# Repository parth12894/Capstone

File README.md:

# Capstone
Code and PCB files for PP01 - 5 Axis CNC Machine Controller
* The main code files for the project are located in /master/CNC/CNC/CNC_5AXIS

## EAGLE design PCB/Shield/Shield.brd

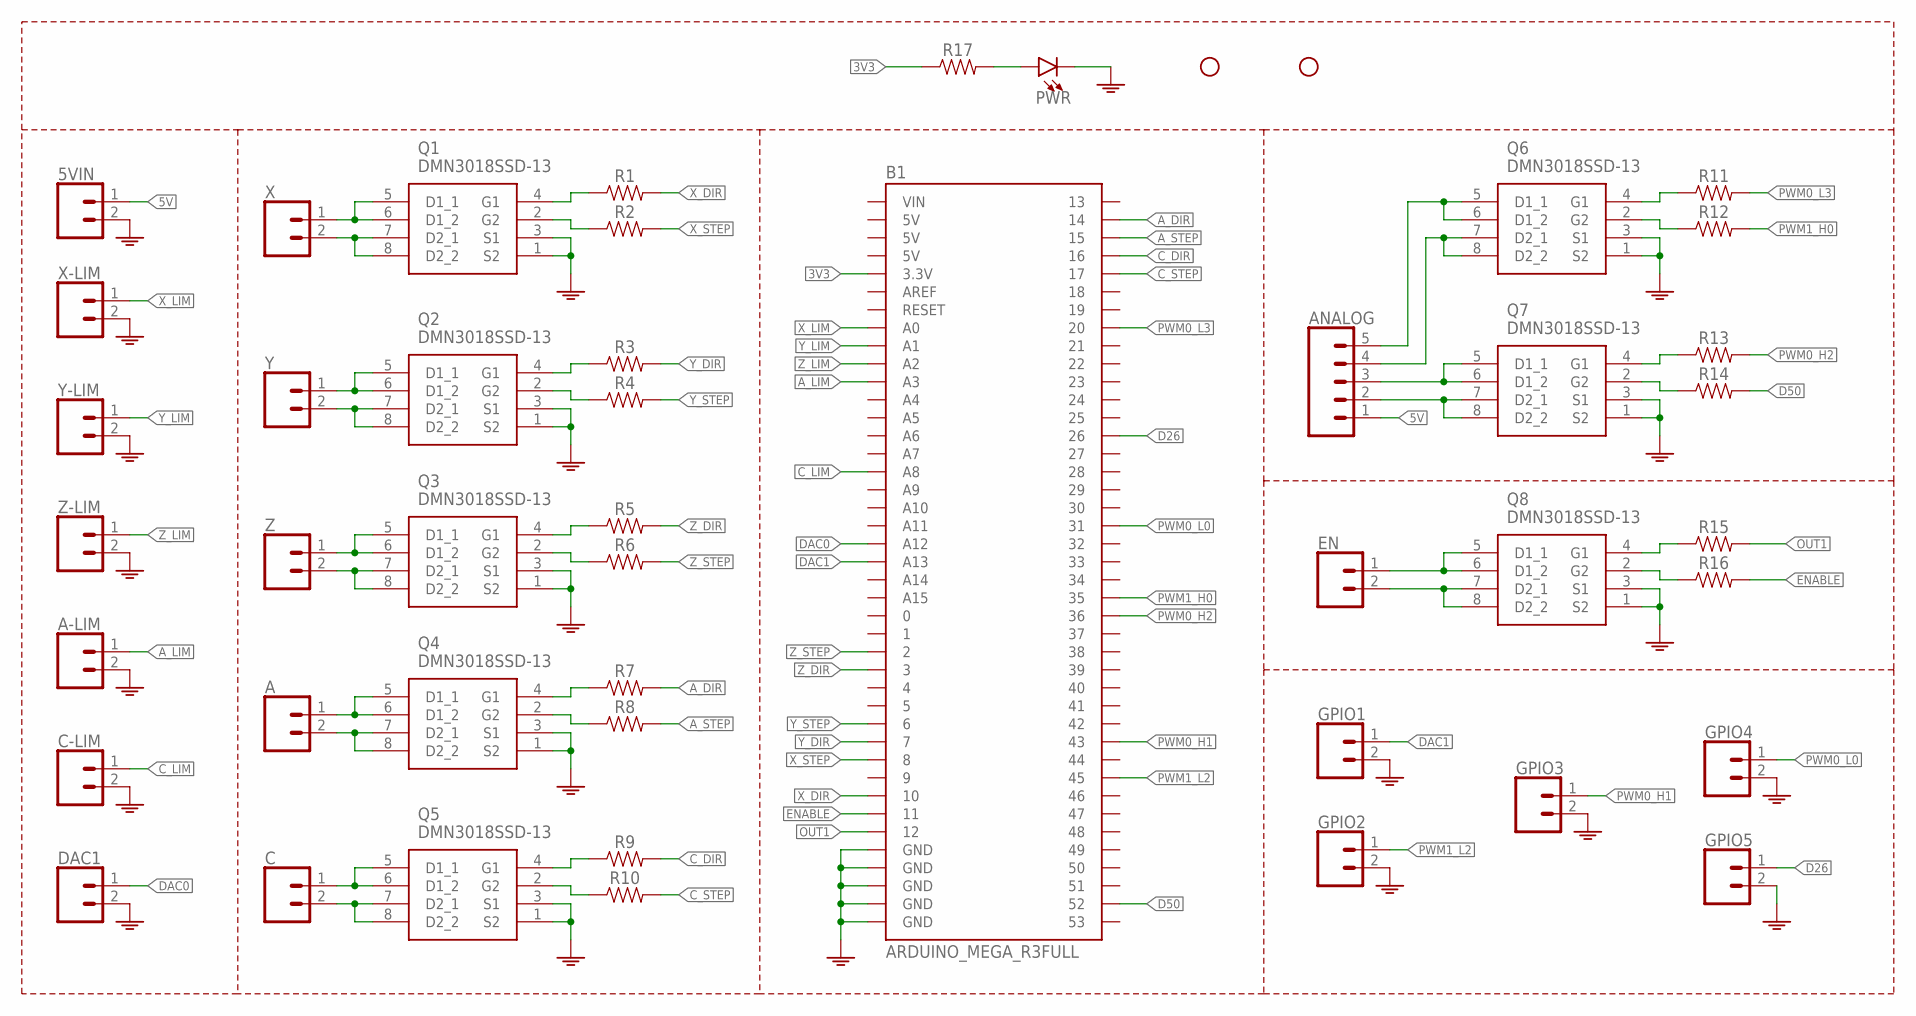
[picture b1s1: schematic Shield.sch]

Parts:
5VIN: 2P-SCREWTERMINAL-PLUGABLE; SCREWTERMINAL-3.5MM-2_LOCK
A: 2P-SCREWTERMINAL-PLUGABLE; SCREWTERMINAL-3.5MM-2_LOCK
A-LIM: 2P-SCREWTERMINAL-PLUGABLE; SCREWTERMINAL-3.5MM-2_LOCK
ANALOG: JST-XH-5P
B1: ARDUINO_MEGA_R3FULL; ARDUINO_MEGA
C: 2P-SCREWTERMINAL-PLUGABLE; SCREWTERMINAL-3.5MM-2_LOCK
C-LIM: 2P-SCREWTERMINAL-PLUGABLE; SCREWTERMINAL-3.5MM-2_LOCK
DAC1: 2P-SCREWTERMINAL-PLUGABLE; SCREWTERMINAL-3.5MM-2_LOCK
EN: 2P-SCREWTERMINAL-PLUGABLE; SCREWTERMINAL-3.5MM-2_LOCK
GPIO1, GPIO2, GPIO3, GPIO4, GPIO5: 2P-SCREWTERMINAL-PLUGABLE; SCREWTERMINAL-3.5MM-2_LOCK
H1, H2: STAND-OFF
PWR: LED-1206; LED_1206
Q1, Q2, Q3, Q4, Q5, Q6, Q7, Q8: DMN3018SSD-13; SOIC127P600X175-8N
R1, R2, R3, R4, R5, R6, R7, R8, R9, R10, R11, R12, R13, R14, R15, R16, R17: RESISTOR-SMD-1206; RES_1206
X: 2P-SCREWTERMINAL-PLUGABLE; SCREWTERMINAL-3.5MM-2_LOCK
X-LIM: 2P-SCREWTERMINAL-PLUGABLE; SCREWTERMINAL-3.5MM-2_LOCK
Y: 2P-SCREWTERMINAL-PLUGABLE; SCREWTERMINAL-3.5MM-2_LOCK
Y-LIM: 2P-SCREWTERMINAL-PLUGABLE; SCREWTERMINAL-3.5MM-2_LOCK
Z: 2P-SCREWTERMINAL-PLUGABLE; SCREWTERMINAL-3.5MM-2_LOCK
Z-LIM: 2P-SCREWTERMINAL-PLUGABLE; SCREWTERMINAL-3.5MM-2_LOCK

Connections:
3V3: B1.3.3V, R17.1
5V: 5VIN.1, ANALOG.1
AGND: 5VIN.2, A-LIM.2, B1.GND@0 (GND), B1.GND@1 (GND), B1.GND@2 (GND), B1.GND@3 (GND), B1.GND@4 (GND), C-LIM.2, DAC1.2, GPIO1.2, GPIO2.2, GPIO3.2, GPIO4.2, GPIO5.2, PWR.C, Q1.1 (S2), Q1.3 (S1), Q2.1 (S2), Q2.3 (S1), Q3.1 (S2), Q3.3 (S1), Q4.1 (S2), Q4.3 (S1), Q5.1 (S2), Q5.3 (S1), Q6.1 (S2), Q6.3 (S1), Q7.1 (S2), Q7.3 (S1), Q8.1 (S2), Q8.3 (S1), X-LIM.2, Y-LIM.2, Z-LIM.2
A_DIR: B1.14, R7.2
A_LIM: A-LIM.1, B1.A3
A_STEP: B1.15, R8.2
C_DIR: B1.16, R9.2
C_LIM: B1.A8, C-LIM.1
C_STEP: B1.17, R10.2
D26: B1.26, GPIO5.1
D50: B1.52, R14.2
DAC0: B1.A12, DAC1.1
DAC1: B1.A13, GPIO1.1
ENABLE: B1.11, R16.2
unnamed: Q1.7 (D2_1), Q1.8 (D2_2), X.2
unnamed: Q1.5 (D1_1), Q1.6 (D1_2), X.1
unnamed: Q2.7 (D2_1), Q2.8 (D2_2), Y.2
unnamed: EN.2, Q8.7 (D2_1), Q8.8 (D2_2)
unnamed: Q1.2 (G2), R2.1
unnamed: Q1.4 (G1), R1.1
unnamed: EN.1, Q8.5 (D1_1), Q8.6 (D1_2)
unnamed: Q2.5 (D1_1), Q2.6 (D1_2), Y.1
unnamed: Q2.2 (G2), R4.1
unnamed: Q8.2 (G2), R16.1
unnamed: Q8.4 (G1), R15.1
unnamed: Q2.4 (G1), R3.1
unnamed: Q3.7 (D2_1), Q3.8 (D2_2), Z.2
unnamed: Q3.5 (D1_1), Q3.6 (D1_2), Z.1
unnamed: PWR.A, R17.2
unnamed: Q3.2 (G2), R6.1
unnamed: Q3.4 (G1), R5.1
unnamed: A.2, Q4.7 (D2_1), Q4.8 (D2_2)
unnamed: A.1, Q4.5 (D1_1), Q4.6 (D1_2)
unnamed: Q4.2 (G2), R8.1
unnamed: Q4.4 (G1), R7.1
unnamed: C.2, Q5.7 (D2_1), Q5.8 (D2_2)
unnamed: C.1, Q5.5 (D1_1), Q5.6 (D1_2)
unnamed: Q5.2 (G2), R10.1
unnamed: Q5.4 (G1), R9.1
unnamed: ANALOG.4, Q6.7 (D2_1), Q6.8 (D2_2)
unnamed: ANALOG.5, Q6.5 (D1_1), Q6.6 (D1_2)
unnamed: Q6.2 (G2), R12.1
unnamed: Q6.4 (G1), R11.1
unnamed: ANALOG.2, Q7.7 (D2_1), Q7.8 (D2_2)
unnamed: ANALOG.3, Q7.5 (D1_1), Q7.6 (D1_2)
unnamed: Q7.2 (G2), R14.1
unnamed: Q7.4 (G1), R13.1
OUT1: B1.12, R15.2
PWM0_H1: B1.43, GPIO3.1
PWM0_H2: B1.36, R13.2
PWM0_L0: B1.31, GPIO4.1
PWM0_L3: B1.20, R11.2
PWM1_H0: B1.35, R12.2
PWM1_L2: B1.45, GPIO2.1
X_DIR: B1.10, R1.2
X_LIM: B1.A0, X-LIM.1
X_STEP: B1.8, R2.2
Y_DIR: B1.7, R3.2
Y_LIM: B1.A1, Y-LIM.1
Y_STEP: B1.6, R4.2
Z_DIR: B1.3, R5.2
Z_LIM: B1.A2, Z-LIM.1
Z_STEP: B1.2, R6.2

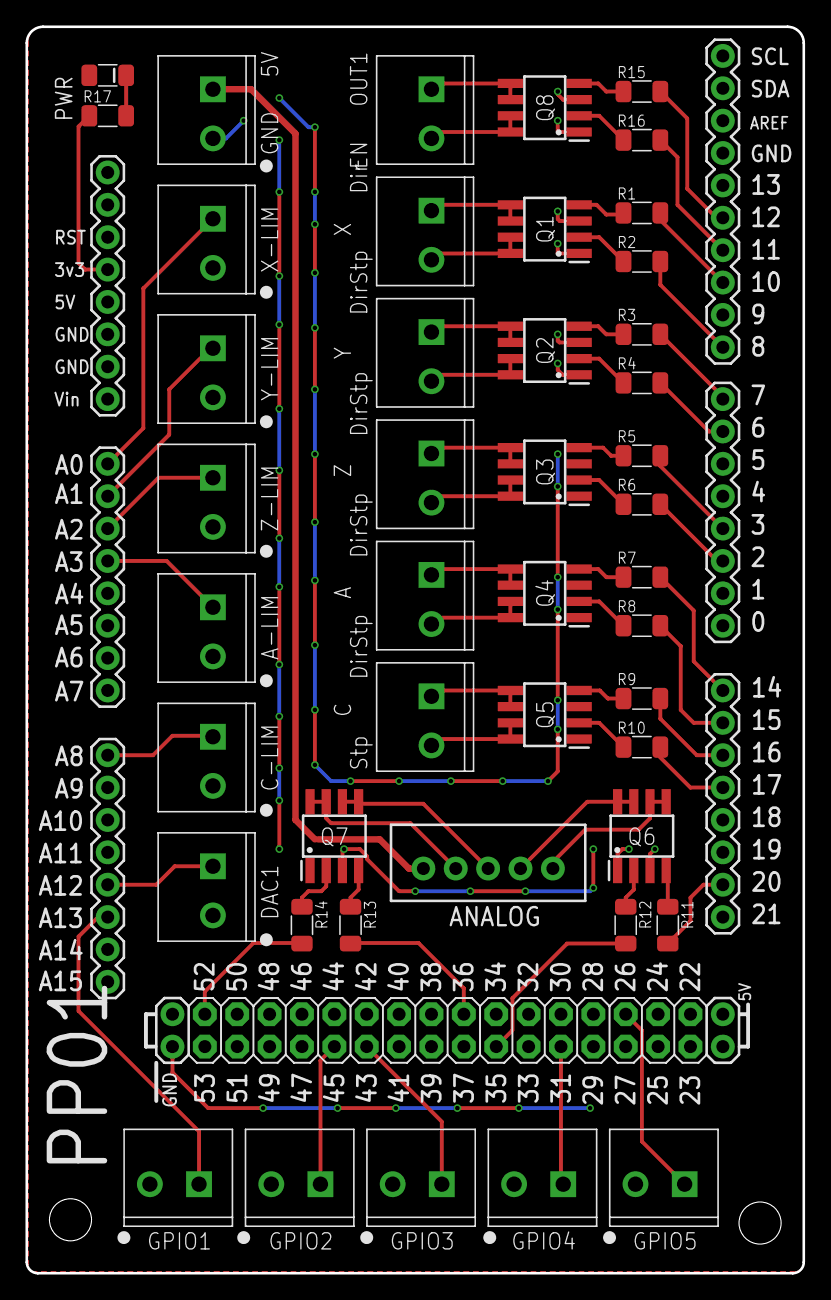
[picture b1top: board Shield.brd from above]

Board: 2 copper layers, 61.0 x 97.8 mm, 48 parts (0 on the bottom side), 63 nets.

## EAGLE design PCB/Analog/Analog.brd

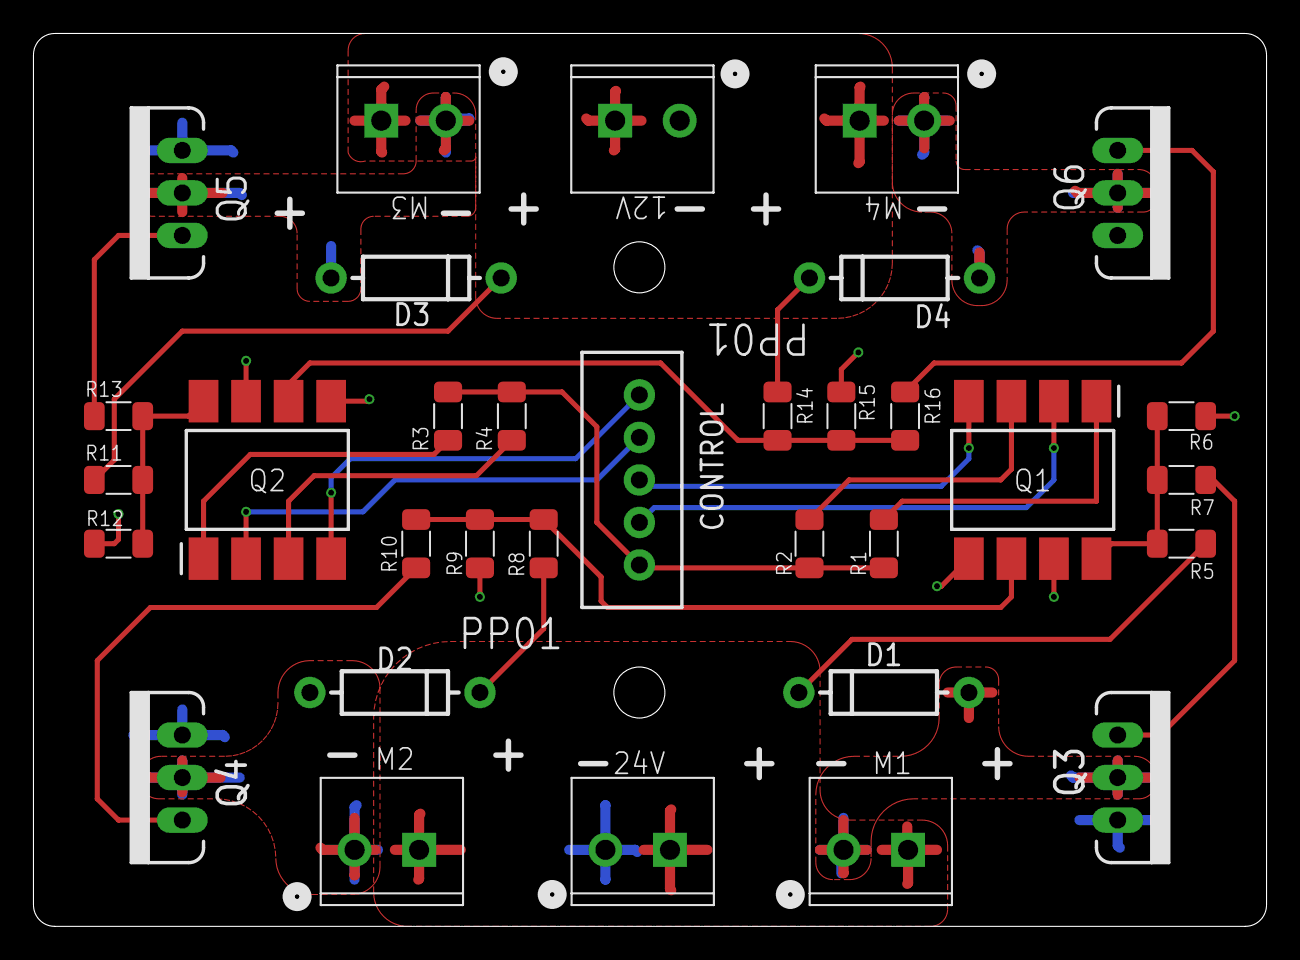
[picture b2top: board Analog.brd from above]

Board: 2 copper layers, 73.7 x 53.3 mm, 35 parts (0 on the bottom side), 25 nets.

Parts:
12V, 24V: 2P-SCREWTERMINAL-PLUGABLE; SCREWTERMINAL-3.5MM-2_LOCK
CONTROL: JST-XH-5P
D1, D2, D3, D4: DIODE-1N4001-KIT
M1, M2, M3, M4: 2P-SCREWTERMINAL-PLUGABLE; SCREWTERMINAL-3.5MM-2_LOCK
Q1, Q2: PDIP8-GULLWING
Q3, Q4, Q5, Q6: TO220V
R1, R2, R3, R4, R5, R6, R7, R8, R9, R10, R11, R12, R13, R14, R15, R16: RES_1206
U$1, U$2: STANDOFF; STAND-OFF-TIGHT

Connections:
5V: CONTROL.1, R1.1, R2.1, R3.1, R4.1
12V: 12V.1, D3.C, D4.C, M3.1, M4.1, R11.2, R14.2
24V: 24V.1, D1.C, D2.C, M1.1, M2.1, R5.2, R8.2
AGND: 24V.2, Q1.5, Q1.7, Q3.S, Q4.S, R6.1, R9.1
CO1: Q1.8, R5.1, R6.2, R7.1
CO2: Q1.6, R8.1, R9.2, R10.1
CO3: Q2.8, R11.1, R12.2, R13.1
CO4: Q2.6, R14.1, R15.2, R16.1
GND: 12V.2, Q2.5, Q2.7, Q5.S, Q6.S, R12.1, R15.1
unnamed: CONTROL.2, Q1.2
unnamed: Q1.1, R1.2
unnamed: Q1.3, R2.2
unnamed: CONTROL.3, Q1.4
unnamed: D1.A, M1.2, Q3.D
unnamed: Q3.G, R7.2
unnamed: Q2.1, R3.2
unnamed: CONTROL.4, Q2.2
unnamed: CONTROL.5, Q2.4
unnamed: D2.A, M2.2, Q4.D
unnamed: Q2.3, R4.2
unnamed: D3.A, M3.2, Q5.D
unnamed: Q4.G, R10.2
unnamed: Q5.G, R13.2
unnamed: D4.A, M4.2, Q6.D
unnamed: Q6.G, R16.2

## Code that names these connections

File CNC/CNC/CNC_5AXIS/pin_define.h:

#ifndef PIN_DEFINE_H_
#define PIN_DEFINE_H_

// SDMMC I/O
#define D33 MCDA2
#define D41	MCDA1
#define D44	MCCK
#define D48	MCDA0
#define D49 MCCDA


// USART for Serial Comm.
#define D46	RX
#define D47	TX


// PWM Outputs
#define D31 PWM0_L0 // GPIO 4
#define D45 PWM0_H1 // GPIO 2
#define D36 PWM0_H2 // M2
#define D20	PWM0_L3 // M4

#define D35 PWM1_H0 // M3
#define D43	PWM1_L2 // GPIO 3


// Analog Outputs
#define A12	DAC0	
#define A13	DAC1	// GPIO1


// Digital Outputs
#define OUT1	D12
#define ENABLE  D11
#define X_DIR   D10
#define X_STEP  D8
#define Y_DIR   D7
#define Y_STEP  D6
#define Z_DIR   D3
#define Z_STEP  D2
#define A_DIR   D14
#define A_STEP  D15
#define C_DIR	D16
#define C_STEP  D17


// Digital Inputs
#define X_LIM	A0
#define Y_LIM	A1
#define Z_LIM	A2
#define A_LIM	A3
#define C_LIM	A8


// Analog board connections
#define M1 D52		
#define M2 D36		// PWM0_H2
#define M3 D35		// PWM1_H0
#define M4 D20		// PWM0_L3

#define FLOOD_COOLANT M1
#define MIST_COOLANT M2
#define SPINDLE	M3

#define GPIO1 A13	// DAC1
#define GPIO2 D45	// PWM0_H1
#define GPIO3 D43	// PWM1_L2
#define GPIO4 D31	// PWM0_L0
#define GPIO5 D26

#endif

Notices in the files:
parts and their libraries:
SparkFun-Hardware: Licensing: Creative Commons ShareAlike 4.0 International - https://creativecommons.org/licenses/by-sa/4.0
